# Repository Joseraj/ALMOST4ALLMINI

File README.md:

Welcome to the ALMOST4ALLMINI wiki!

# ALMOST4ALLMINI
Arduino Mini board for [Mysensors](http://www.mysensors.org/)

This board is intended to be valid for almost any sensor/node available on mysensors site.

I hate to fight sharing 1 pin for the grounds.
The main goal is to have on the board independent connectors for every sensor that i want to use in one node.

The board can be powered with battery (from 0,9 to 6,5V), 3.3V or 5V regulated.
The Arduino pro mini is powered with 3.3V or battery, so that is the reference for analog I/O. (No 5V)

There is the possibility of using some SMD resistors, capacitors and ICs. All of this are optional, but adding this hardware on board allows to use more simple and economic sensors and some extras (low cost temperature sensor, battery monitor, external eprom, signing)

[Hardware](http://www.mysensors.org/)

[Power](/wiki/Power)

Sensors and software:

[Door, Window and Push-button Sensor](../wiki/Door,-Window-and-Push-button-Sensor/)

[Distance Sensor](../wiki/Distance-Sensor)

[Real Time Clock Module, LCD Display and Controller Time](../wiki/Real-Time-Clock-Module,-LCD-Display-and-Controller-Time)

[Dust Level Sensor](../wiki/Dust-Level-Sensor)

[Gas Sensor](../wiki/Gas-Sensor)

[Humidity Sensor](../wiki/Humidity-Sensor)

[Infrared Sender and Receiver](../wiki/Infrared-Sender-and-Receiver)

[Light Sensor](http://www.mysensors.org/)

[Moisture Sensor](http://www.mysensors.org/)

[Motion Sensor](http://www.mysensors.org/)

[Pressure Sensor](http://www.mysensors.org/)

[Parking Sensor](http://www.mysensors.org/)

[Power Meter Pulse Sensor](http://www.mysensors.org/)

[Water Meter Pulse Sensor](http://www.mysensors.org/)

[Rain Gauge](http://www.mysensors.org/)

[Relay Actuator](http://www.mysensors.org/)

[RFID Lock Sensor](http://www.mysensors.org/)

[Secret Knock Sensor](http://www.mysensors.org/)

[Servo Control Actuator](http://www.mysensors.org/)

[Temperature Sensor](http://www.mysensors.org/)

[UV Sensor](http://www.mysensors.org/)

Extras:

[Temperature Sensor (NTC)](http://www.mysensors.org/)

[Light Sensor (LDR)](http://www.mysensors.org/)

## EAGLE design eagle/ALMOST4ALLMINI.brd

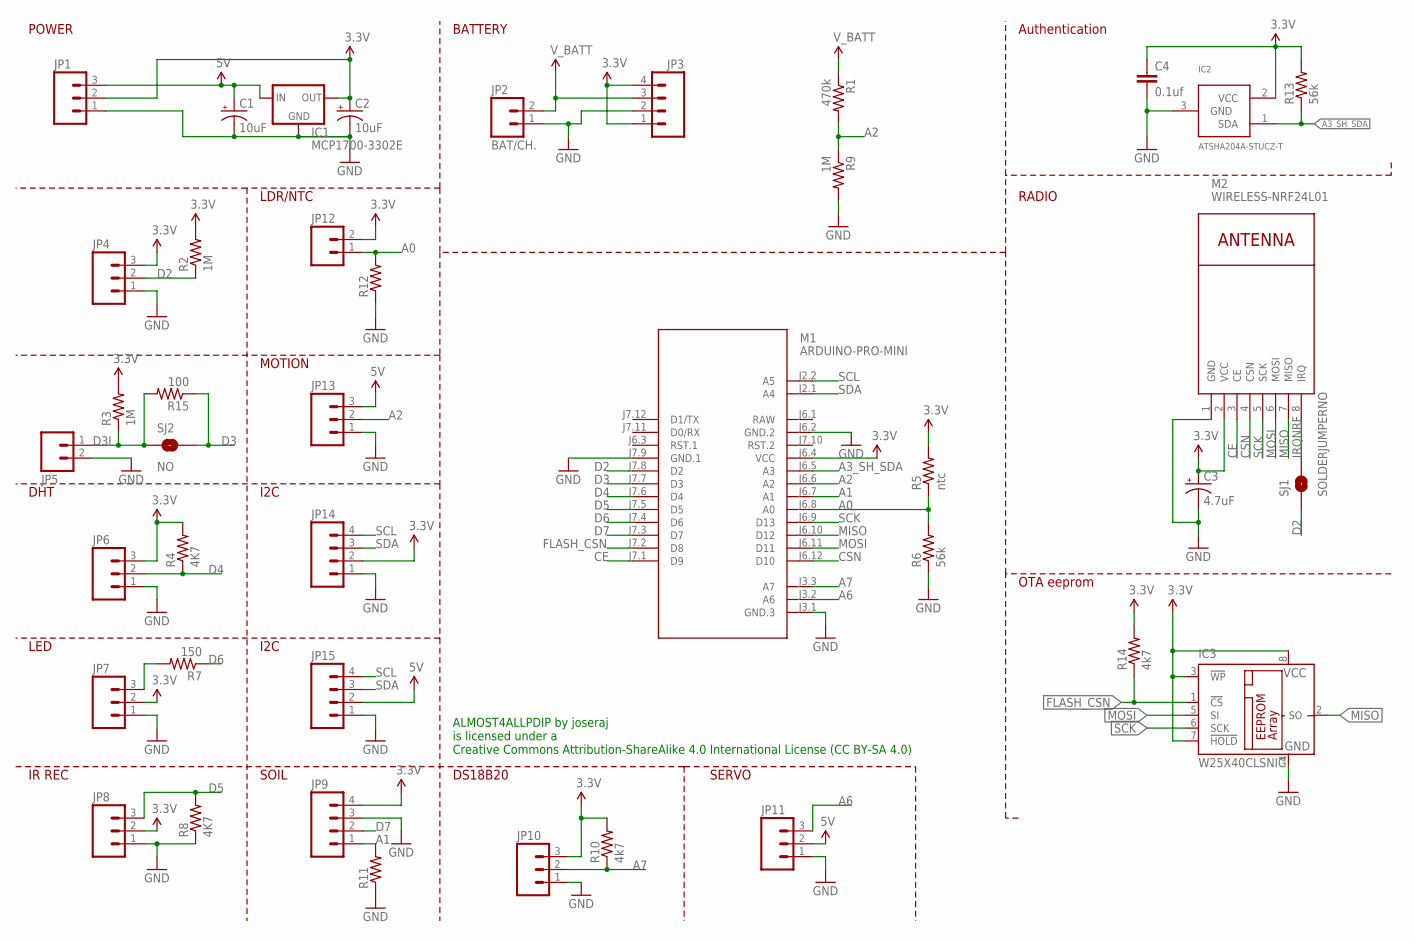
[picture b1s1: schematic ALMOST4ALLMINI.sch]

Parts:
C1, C2: 10uF; CPOL-RADIAL-10UF-25V
C3: 4.7uF; CPOL-RADIAL-10UF-25V
C4: 0.1uf; 0805
IC1: MCP1700-3302E; TO92
IC2: ATSHA204A-STUCZ-T; SOT23
IC3: W25X40CLSNIG; SO-08
JP1, JP4, JP6, JP7, JP8, JP10, JP11, JP13: M03POLAR_LOCK; MOLEX-1X3_LOCK
JP2: BAT/CH.; MOLEX-1X2_LOCK
JP3: M04NO_SILK_ALL_ROUND; 1X04_NO_SILK_ALL_ROUND
JP5, JP12: M02POLAR_LOCK; MOLEX-1X2_LOCK
JP9, JP14, JP15: M04POLAR_LOCK; MOLEX-1X4_LOCK
M1: ARDUINO-PRO-MINI; ARDUINO-PRO-MINI#NP
M2: WIRELESS-NRF24L01
R1: 470k; 0805
R2, R3, R9: 1M; 0805
R4, R8: 4K7; 0805
R5: ntc; 0805
R6, R13: 56k; 0805
R7: 150; 0805
R10, R14: 4k7; 0805
R11, R12: RESISTOR0805-RES; 0805
R15: 100; 0805
SJ1: SOLDERJUMPERNO; SJ_2S-NO
SJ2: NO; SJ_2S-NO

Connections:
3.3V: C2.1 (+), C3.1 (+), C4.1, IC1.3 (OUT), IC2.2 (VCC), IC3.3 (!WP), IC3.7 (!HOLD), IC3.8 (VCC), JP1.2, JP3.1, JP3.4, JP4.3, JP6.3, JP7.2, JP8.2, JP9.4, JP10.3, JP12.2, JP14.2, M1.J6.4 (VCC), M2.2 (VCC), R2.2, R3.2, R4.2, R5.2, R10.2, R13.2, R14.2
5V: C1.1 (+), IC1.2 (IN), JP1.3, JP11.2, JP13.3, JP15.2
A0: JP12.1, M1.J6.8 (A0), R5.1, R6.2, R12.2
A1: JP9.1, M1.J6.7 (A1), R11.2
A2: JP13.2, M1.J6.6 (A2), R1.2, R9.1
A3_SH_SDA: IC2.1 (SDA), M1.J6.5 (A3), R13.1
A6: JP11.3, M1.J3.2 (A6)
A7: JP10.2, M1.J3.3 (A7), R10.1
CE: M1.J7.1 (D9), M2.3 (CE)
CSN: M1.J6.12 (D10), M2.4 (CSN)
D2: JP4.2, M1.J7.8 (D2), R2.1, SJ1.1
D3: M1.J7.7 (D3), R15.1, SJ2.2
D3I: JP5.1, R3.1, R15.2, SJ2.1
D4: JP6.2, M1.J7.6 (D4), R4.1
D5: JP8.3, M1.J7.5 (D5), R8.2
D6: M1.J7.4 (D6), R7.1
D7: JP9.2, M1.J7.3 (D7)
FLASH_CSN: IC3.1 (!CS), M1.J7.2 (D8), R14.1
GND: C1.2 (-), C2.2 (-), C3.2 (-), C4.2, IC1.1 (GND), IC2.3 (GND), IC3.4 (GND), JP1.1, JP2.1, JP3.2, JP4.1, JP5.2, JP6.1, JP7.1, JP8.1, JP9.3, JP10.1, JP11.1, JP13.1, JP14.1, JP15.1, M1.J3.1 (GND.3), M1.J6.2 (GND.2), M1.J7.9 (GND.1), M2.1 (GND), R6.1, R8.1, R9.2, R11.1, R12.1
IRQNRF: M2.8 (IRQ), SJ1.2
MISO: IC3.2 (SO), M1.J6.10 (D12), M2.7 (MISO)
MOSI: IC3.5 (SI), M1.J6.11 (D11), M2.6 (MOSI)
unnamed: JP7.3, R7.2
RAW: M1.J6.1 (RAW)
SCK: IC3.6 (SCK), M1.J6.9 (D13), M2.5 (SCK)
SCL: JP14.4, JP15.4, M1.J2.2 (A5)
SDA: JP14.3, JP15.3, M1.J2.1 (A4)
V_BATT: JP2.2, JP3.3, R1.1

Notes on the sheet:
I2C
DHT
IR REC
LED
SOIL
MOTION
SERVO
DS18B20
LDR/NTC
BATTERY
POWER
Authentication
RADIO
OTA eeprom
ALMOST4ALLPDIP by joseraj is licensed under a Creative Commons Attribution-ShareAlike 4.0 International License (CC BY-SA 4.0)

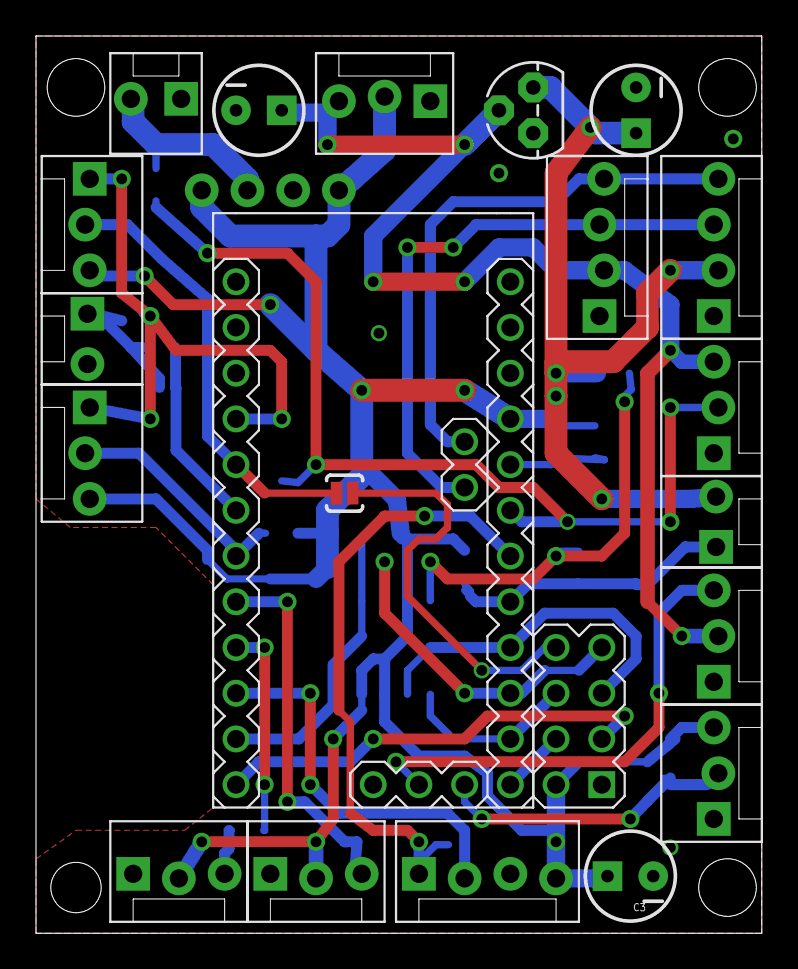
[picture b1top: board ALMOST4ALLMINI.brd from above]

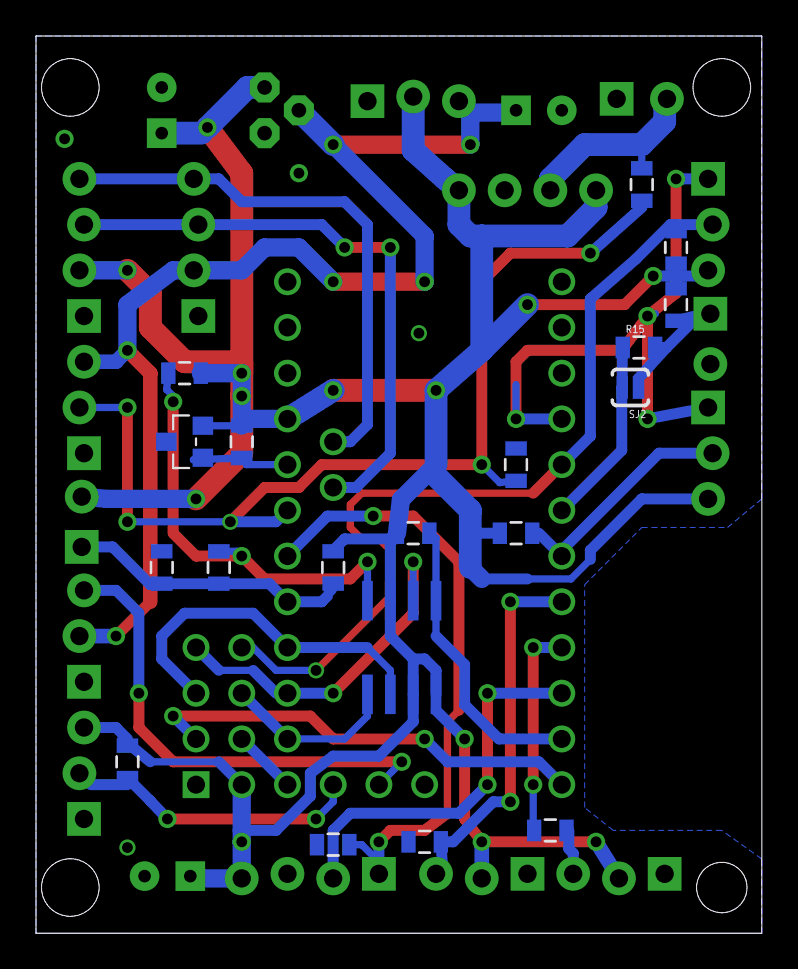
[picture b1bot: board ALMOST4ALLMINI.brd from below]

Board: 2 copper layers, 40.3 x 49.8 mm, 41 parts (19 on the bottom side), 27 nets.

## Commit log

2016-02-06 Upload eagle files
2016-02-06 Copy Mysensors 1.5 Examples
2016-02-06 Changed structure tree
2016-02-06 added images
2016-02-06 added gerber files
2016-02-06 added license
2016-02-06 Starting Readme
2016-02-13 Deleted wrong file
2016-02-13 56K values IR-Send corrected
2016-02-13 Examples

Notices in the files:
parts and their libraries:
SparkFun-Aesthetics: Licensing: Creative Commons ShareAlike 4.0 International - https://creativecommons.org/licenses/by-sa/4.0
diy-modules: Released under the Creative Commons Attribution 4.0 International License: http://creativecommons.org/licenses/by/4.0
